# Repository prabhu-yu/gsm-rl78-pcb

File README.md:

# GSM-RL78-PCB

- Designed using KiCAD PCB Design SW.
- GSM modem Interface to RL78 uC using AT-MODEM commands over UART. Using this, we can build 2G/3G/4G wireless automation device. 
    - For example: to switch a remote high power motors, to monitor status using SMS/phone call. 
- The embedded C code to issue GSM AT Commands is available in another repo in my same gitHub account.

I plan to write a better documentation on my personal site:  
[https://prabhu-yu.github.io/](https://prabhu-yu.github.io/)

-
Thank You.  
Prabhu. Ullagaddi.

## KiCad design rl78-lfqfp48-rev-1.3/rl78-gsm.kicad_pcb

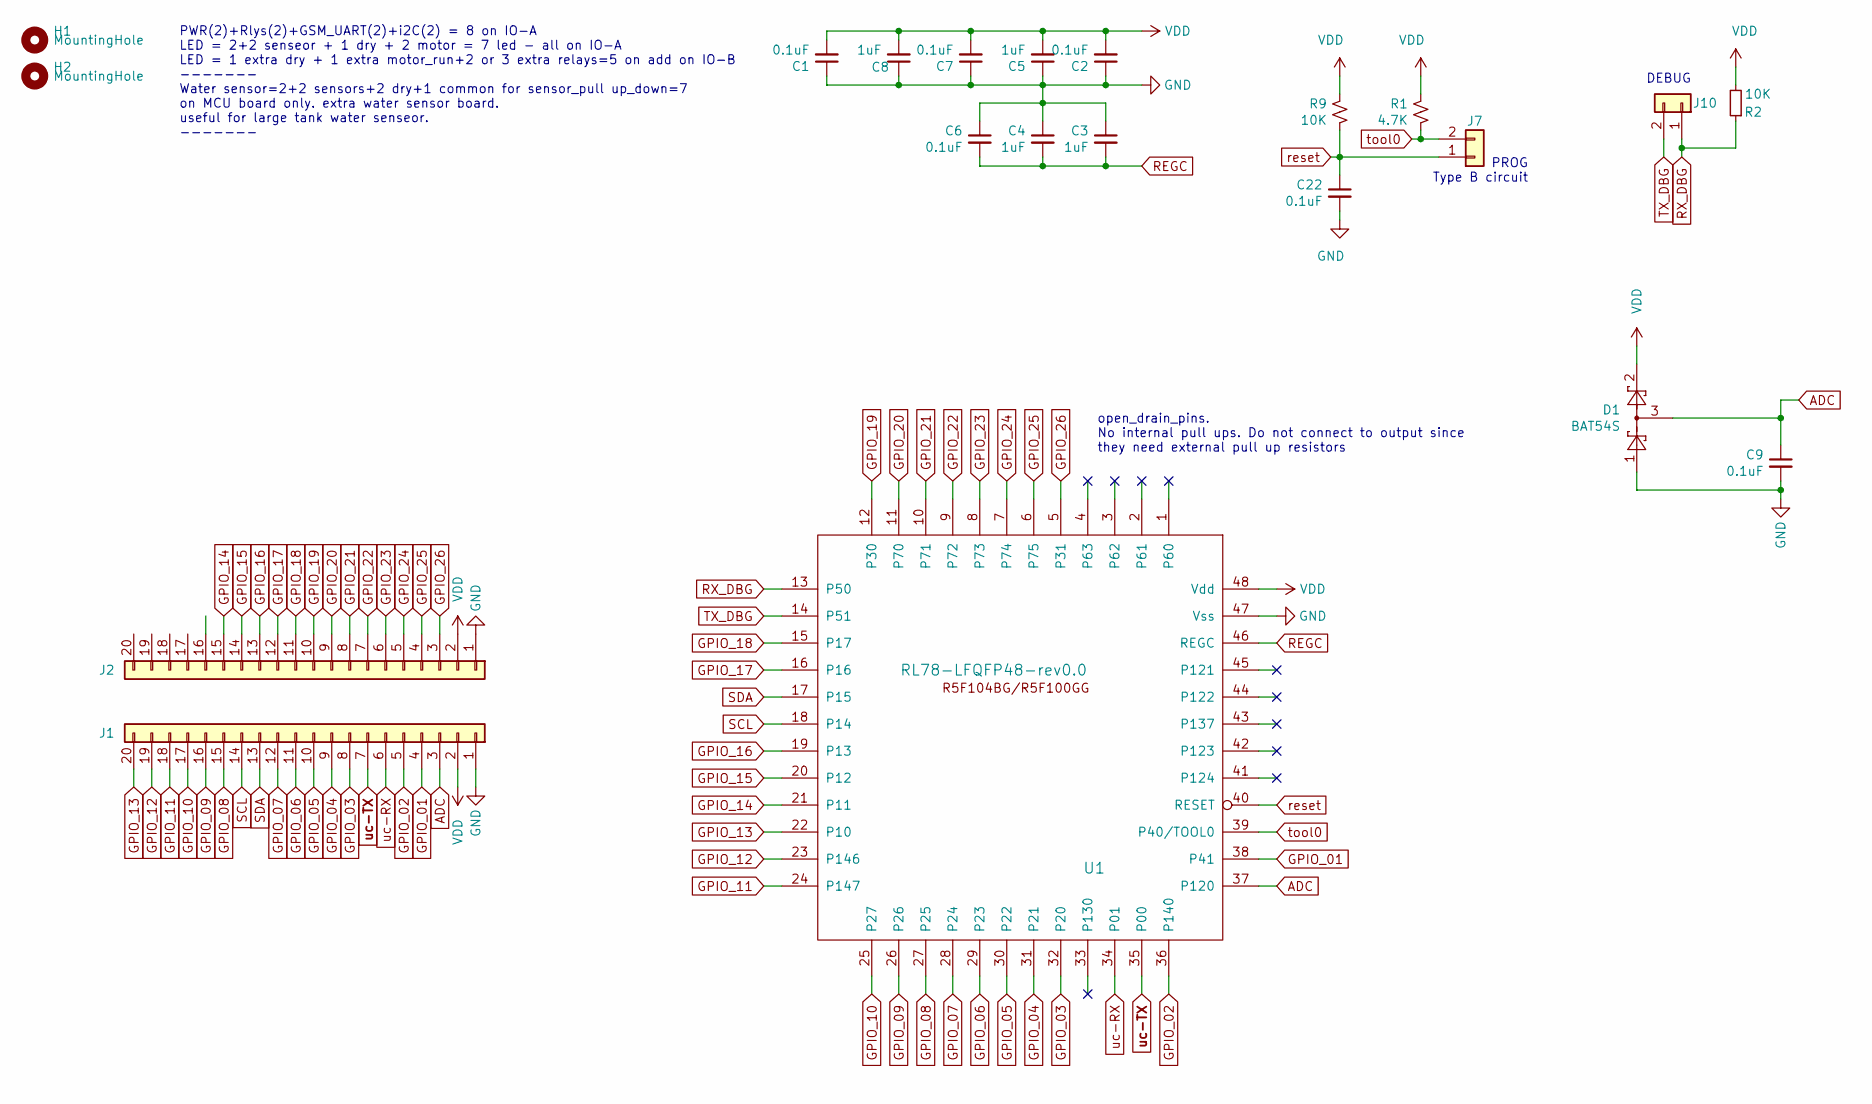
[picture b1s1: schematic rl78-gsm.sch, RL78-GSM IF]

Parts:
C1, C2, C6, C7, C9, C22: 0.1uF; C_1206_3216Metric_Pad1.33x1.80mm_HandSolder
C3, C4, C5, C8: 1uF; C_1206_3216Metric_Pad1.33x1.80mm_HandSolder
D1: BAT54S; SOT-23
H1, H2: MountingHole; MountingHole_4mm
J1, J2: Conn_01x20; PinHeader_1x20_P2.54mm_Vertical
J7, J10: Conn_01x02; PinHeader_1x02_P2.54mm_Vertical
R1: 4.7K; R_1206_3216Metric_Pad1.30x1.75mm_HandSolder
R2, R9: 10K; R_1206_3216Metric_Pad1.30x1.75mm_HandSolder
U1: RL78-LFQFP48-rev0.0; LQFP-48_7x7mm_P0.5mm

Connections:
ADC: C9.1, D1.3, J1.3, U1.37 (P120)
GND: C1.1, C2.1, C3.1, C4.1, C5.1, C6.1, C7.1, C8.1, C9.2, C22.2, D1.1, J1.1, J2.1, U1.47 (Vss)
GPIO_01: J1.4, U1.38 (P41)
GPIO_02: J1.5, U1.36 (P140)
GPIO_03: J1.8, U1.32 (P20)
GPIO_04: J1.9, U1.31 (P21)
GPIO_05: J1.10, U1.30 (P22)
GPIO_06: J1.11, U1.29 (P23)
GPIO_07: J1.12, U1.28 (P24)
GPIO_08: J1.15, U1.27 (P25)
GPIO_09: J1.16, U1.26
GPIO_10: J1.17, U1.25 (P27)
GPIO_11: J1.18, U1.24 (P147)
GPIO_12: J1.19, U1.23 (P146)
GPIO_13: J1.20, U1.22 (P10)
GPIO_14: J2.15, U1.21 (P11)
GPIO_15: J2.14, U1.20 (P12)
GPIO_16: J2.13, U1.19 (P13)
GPIO_17: J2.12, U1.16
GPIO_18: J2.11, U1.15 (P17)
GPIO_19: J2.10, U1.12 (P30)
GPIO_20: J2.9, U1.11 (P70)
GPIO_21: J2.8, U1.10 (P71)
GPIO_22: J2.7, U1.9 (P72)
GPIO_23: J2.6, U1.8 (P73)
GPIO_24: J2.5, U1.7 (P74)
GPIO_25: J2.4, U1.6 (P75)
GPIO_26: J2.3, U1.5 (P31)
REGC: C3.2, C4.2, C6.2, U1.46 (REGC)
RX_DBG: J10.1, R2.1, U1.13 (P50)
SCL: J1.14, U1.18 (P14)
SDA: J1.13, U1.17 (P15)
TX_DBG: J10.2, U1.14 (P51)
VDD: C1.2, C2.2, C5.2, C7.2, C8.2, D1.2, J1.2, J2.2, R1.2, R2.2, R9.2, U1.48 (Vdd)
reset: C22.1, J7.1, R9.1, U1.40 (RESET)
tool0: J7.2, R1.1, U1.39 (P40/TOOL0)
uc-RX: J1.6, U1.34 (P01)
uc-TX: J1.7, U1.35 (P00)

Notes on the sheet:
PWR(2)+Rlys(2)+GSM_UART(2)+i2C(2) = 8 on IO-A LED = 2+2 senseor + 1 dry + 2 motor = 7 led - all on IO-A LED = 1 extra dry + 1 extra motor_run+2 or 3 extra relays=5 on add on IO-B ------- Water sensor=2+2 sensors+2 dry+1 common for sensor_pull up_down=7 on MCU board only. extra water sensor board. u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
DEBUG
open_drain_pins. No internal pull ups. Do not connect to output since they need external pull up resistors
PROG Type B circuit

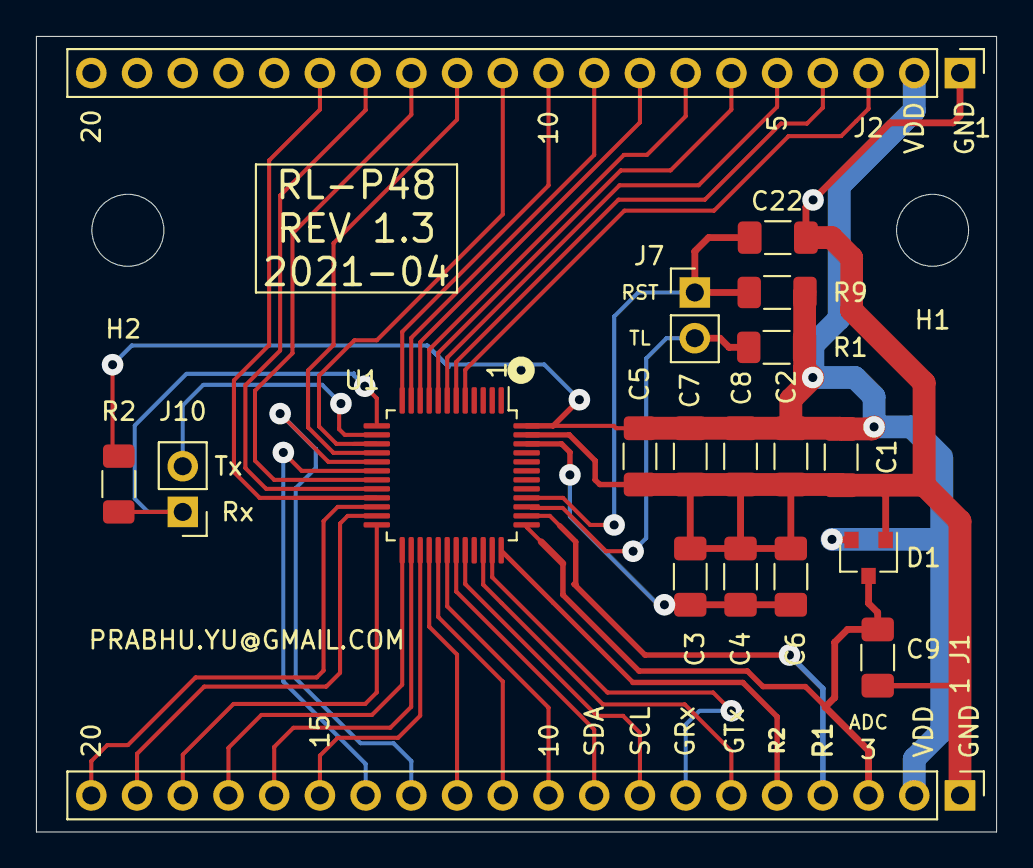
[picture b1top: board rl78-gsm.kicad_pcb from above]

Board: 2 copper layers, 53.3 x 44.2 mm, 21 parts (0 on the bottom side), 38 nets.

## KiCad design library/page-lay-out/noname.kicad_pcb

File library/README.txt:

kicad-library-master is downloaded from
https://github.com/automote/kicad-library

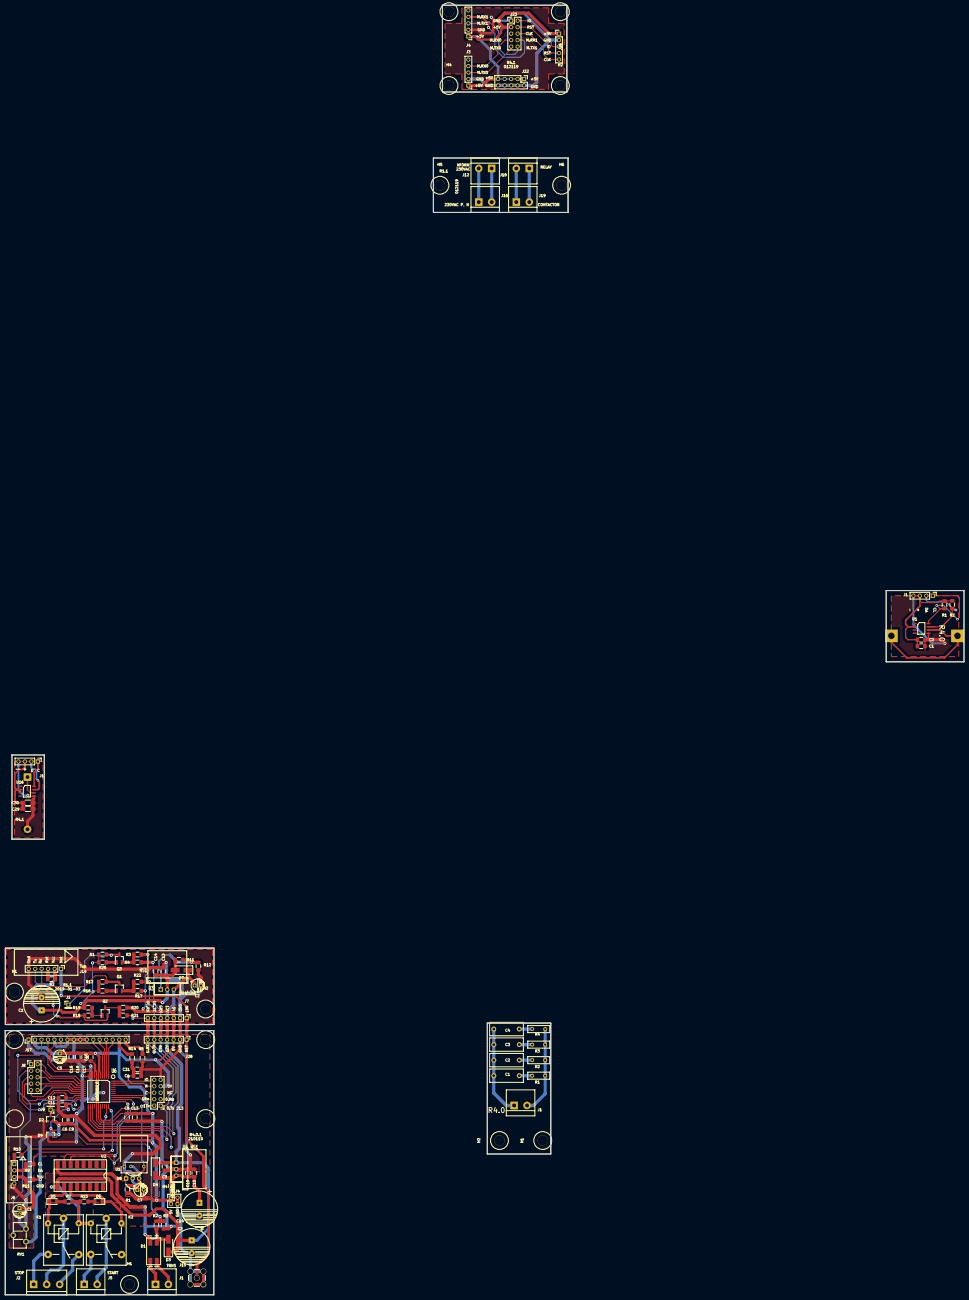
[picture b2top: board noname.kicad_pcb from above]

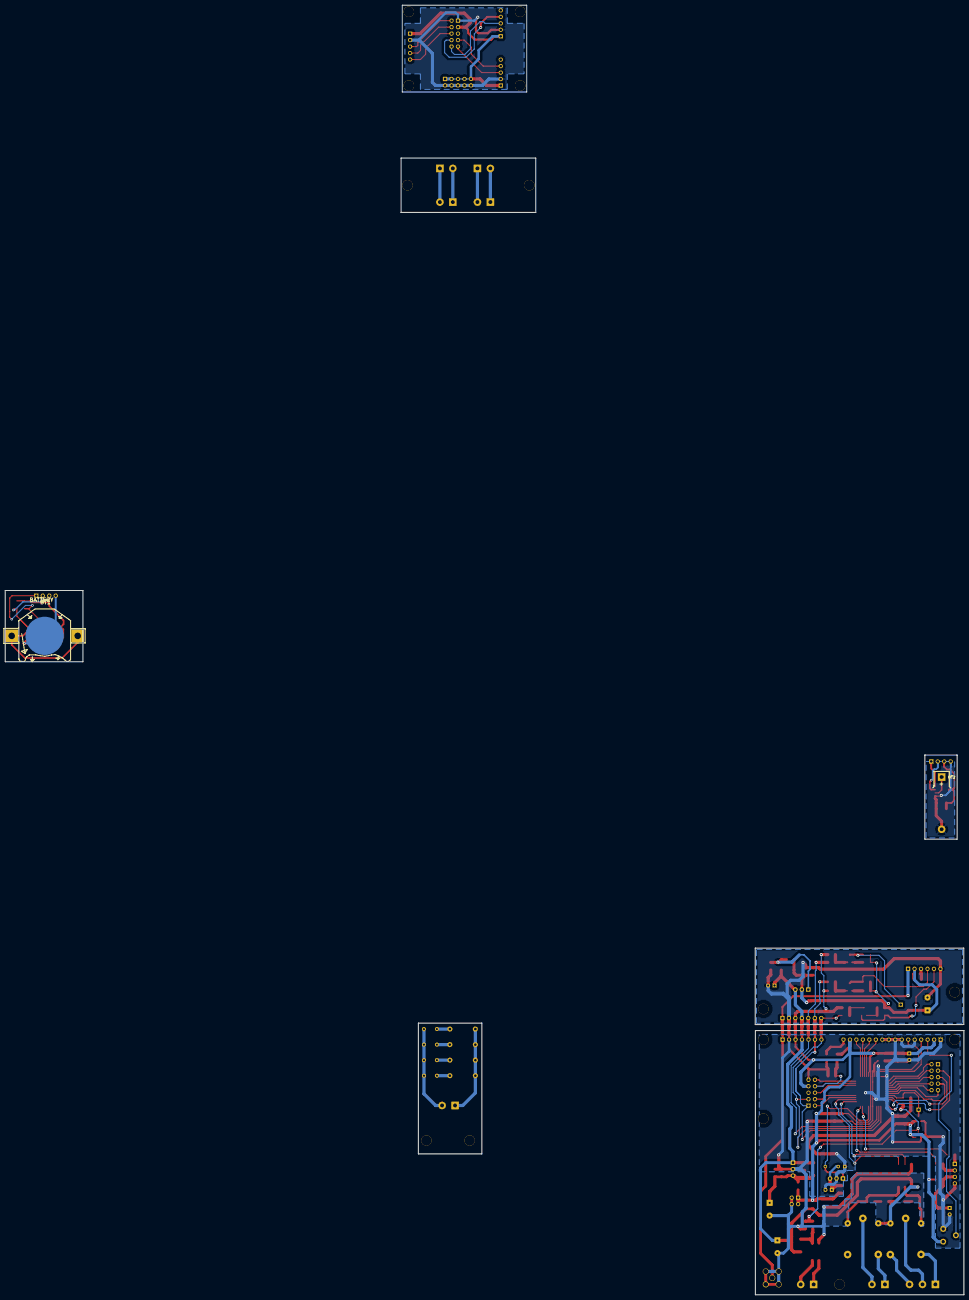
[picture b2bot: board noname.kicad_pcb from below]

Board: 2 copper layers, 376.0 x 505.8 mm, 127 parts (2 on the bottom side), 96 nets.

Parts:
BT1: BATTERY; BC-2001
BT2: BATTERY; Keystone_103_1x20mm-CoinCell-prabhu
C1: 6.8uF+; CP_Radial_D5.0mm_P2.50mm
C1#2: 1000uF/25V; CP_Radial_D14.0mm_P5.00mm
C1#3: C29; C_1206_3216Metric_Pad1.42x1.75mm_HandSolder
C1#4, C2#4, C3#2, C4#2: 0.01uF/X2/Y2; C_Rect_L13.0mm_W5.0mm_P10.00mm_FKS3_FKP3_MKS4
C2: 1000uF/50V; CP_Radial_D14.0mm_P5.00mm
C2#2: 10-100uF/50V; CP_Radial_D5.0mm_P2.50mm
C2#3: C30; C_1206_3216Metric_Pad1.42x1.75mm_HandSolder
C3: 0.1uF; R_1206_3216Metric_Pad1.42x1.75mm_HandSolder
C4, C8, C10, C14#2, C16, C18: 0.1uF; C_1206_3216Metric_Pad1.42x1.75mm_HandSolder
C5: 100uF; CP_Radial_D5.0mm_P2.50mm
C6, C9, C13, C13#2, C15, C17, C19, C31: 1uF; C_1206_3216Metric_Pad1.42x1.75mm_HandSolder
C7: 4.7uF/10V; CP_Radial_D5.0mm_P2.50mm
C11, C12: 0.01uF/ADC; C_1206_3216Metric_Pad1.42x1.75mm_HandSolder
C14: 1000uF/10V; CP_Radial_D14.0mm_P5.00mm
C29: 1uF; R_1206_HandSoldering
C30: 0.1uF; R_1206_HandSoldering
D1: D_Bridge_+-AA; MBXS
D2, D9: BAT54S; SOT-23
D3, D4: M7; D_SMA_Handsoldering
D5, D6: LED_Small; LED_1206_3216Metric_Pad1.42x1.75mm_HandSolder
D7: D; D_SMA_Handsoldering
D8: RPM7140; Vishay_MOLD-3Pin
H1, H1#2, H1#3, H1#4, H2, H2#2, H2#3, H3, H4, H5, H6: MountingHole; MountingHole_4.1x7.1mm
HS1, HS1#2: Heatsink; TO220_VERT-heatSink-Only
J1, J5, J12, J16, J18, J19: Screw_Terminal_1x02; bornier2
J1#2, J9: Conn_01x01; PinHeader_1x01_P2.54mm_Vertical
J1#3: Conn_01x04; Pin_Header_Straight_1x04_Pitch2.54mm
J1#4: Conn_01x04; PinHeader_1x04_P2.54mm_Vertical
J1#5: Screw_Terminal_01x02; bornier2
J2: Screw_Terminal_01x03; bornier3
J3, J4#2, J26: Conn_01x05; PinHeader_1x05_P2.54mm_Vertical
J4: Conn_02x02_Odd_Even; PinHeader_2x02_P2.54mm_Vertical
J6: Conn_01x04; RTC-BERG-V2
J7, J28: Conn_01x07; PinHeader_1x07_P2.54mm_Vertical
J8, J13, J22, J23: Conn_02x05_Odd_Even; PinHeader_2x05_P2.54mm_Vertical
J14: SIM800L-coro-board-v1; SIM800L-CoroBoard-Verticle
J15: Conn_Coaxial; SMA_THT_Jack_Straight
J17: LCD_2X16; LCD-v3
K1, K2: HRS4; Relay_SPDT_SANYOU_SRD_Series_Form_C
Q1, Q2, Q3: BC817; SOT-23_Handsoldering
R1: 60R-100R; R_1206_3216Metric_Pad1.42x1.75mm_HandSolder
R1#2, R26: 4K7-DNP; R_1206_3216Metric_Pad1.42x1.75mm_HandSolder
R1#3, R2#2, R2#3, R18: 47K; R_1206_3216Metric_Pad1.42x1.75mm_HandSolder
R1#4, R2#4, R3#3, R4#3: 100R; R_Box_L8.4mm_W2.5mm_P5.08mm
R2, R4: 1K2; R_1206_3216Metric_Pad1.42x1.75mm_HandSolder
R3: 150R; R_1206_3216Metric_Pad1.42x1.75mm_HandSolder
R3#2: 47K-DNP; R_1206_3216Metric_Pad1.42x1.75mm_HandSolder
R4#2, R20: 4.7K-DNP; R_1206_3216Metric_Pad1.42x1.75mm_HandSolder
R5: 1K+; R_1206_3216Metric_Pad1.42x1.75mm_HandSolder
R7, R14, R15: 10K; R_1206_3216Metric_Pad1.42x1.75mm_HandSolder
R9, R10: 100R-150R; R_1206_3216Metric_Pad1.42x1.75mm_HandSolder
R11: 100R-330R; R_1206_3216Metric_Pad1.42x1.75mm_HandSolder
R11#2: 240R; R_1206_3216Metric_Pad1.42x1.75mm_HandSolder
R12: 560R; R_1206_3216Metric_Pad1.42x1.75mm_HandSolder
R13, R16: 4K7; R_1206_3216Metric_Pad1.42x1.75mm_HandSolder
R17: 47K/pullup?-DNP; R_1206_3216Metric_Pad1.42x1.75mm_HandSolder
R19: 4.7K; R_1206_3216Metric_Pad1.42x1.75mm_HandSolder
R21, R22: 1K; R_1206_3216Metric_Pad1.42x1.75mm_HandSolder
RV1: POT; Potentiometer_ACP_CA9-H5_Horizontal
U1: TSOP17xx; Vishay_CAST-3Pin-Horizontal-V1
U1#2: DS3231MZ-SO8N; SOIC-8_3.9x4.9mm_Pitch1.27mm
U2: ULN2003; DIP-16_W8.89mm_SMDSocket_LongPads
U3: LM317_3PinPackage; TO220_VERT-heat
U4: L7805; TO220_VERT-heat
U6: MKE0XZXXXVLD2_V3; TQFP44-prabhu
U16: DS3231MZ; SOIC-8_3.9x4.9mm_Pitch1.27mm

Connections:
12V_GSM: C2#2.1, D7.1, J7.4, U3.3
+5V: C5.1, C6.2, C8.2, C9.2, C13.2, C15.2, C16.2, C17.2, C18.2, D2.2, D9.2, J3.1, J4.1, J4.3, J4#2.1, J13.7, J17.2, J17.15, J22.1, J22.3, J22.5, J22.7, J22.9, J23.3, J26.1, J28.3, R1.1, R4.2, R11.1, R14.2, RV1.1, U6.5, U6.6, U6.28
+12V: C2.1, C3.1, D3.1, D4.1, J28.4, K1.5, K2.2, R7.2, R15.2, U2.9, U4.1
/5V_GSM: J7.3, R3#2.1, R17.1, R20.1
/DTR: J7.5, R4#2.1
/NET: J7.1, J14.1
/VBAT: BT1.1, U1#2.6
/uc.RX: J7.7, R21.2
/uc.TX: J7.6, R22.2
AC-1: D1.4, J1.2
AC-2: D1.3, J1.1
ADJ: R11#2.1, R12.2, U3.1
CLK: J13.6, U6.42
DBG-CLK: J23.6, J26.5
DBG-IO: J23.2, J26.3
DBG-RST: J23.4, J26.4
DBG-mcu-rx0: J3.4, J23.7
DBG-mcu-rx1: J4#2.4, J23.8
DBG-mcu-tx0: J3.3, J23.9
DBG-mcu-tx1: J4#2.3, J23.10
DIO: J13.10, U6.44
DS3231_GND: BT2.2, C29.1, C30.1, J1#3.4, U16.5
DS3231_SCL: J1#3.1, U16.8
DS3231_SDA: J1#3.2, U16.7
DS3231_VCC: C29.2, C30.2, J1#3.3, U16.2
GND: BT1.2, C1.2, C1#2.2, C1#3.2, C2.2, C2#2.2, C2#3.2, C3.2, C4.1, C5.2, C6.1, C7.2, C8.1, C9.1, C10.2, C11.2, C12.2, C13.1, C13#2.2, C14.2, C14#2.2, C15.1, C16.1, C17.1, C18.1, C19.2, C31.1, D1.2, D2.1, D8.2, D9.1, J1#4.4, J3.2, J4.2, J4.4, J4#2.2, J6.4, J7.2, J13.9, J14.6, J15.2, J17.1, J17.5, J17.7, J17.8, J17.9, J17.10, J22.2, J22.4, J22.6, J22.8, J22.10, J23.1, J26.2, J28.2, R3.1, R5.1, R12.1, RV1.3, U1.1, U1#2.5, U2.8, U4.2, U6.7, U6.8, U6.11, U6.27
GSM.4V2: C1#2.1, C13#2.1, C14#2.1, D7.2, J14.2, R1#2.1, R2#2.1, R11#2.2, R13.1, R16.1, R19.1, R26.1, U3.2
LCD1_RS: J17.4, U6.10
LCD2_EN: J17.6, U6.9
LCD3_DB4: J17.11, U6.4
LCD4_DB5: J17.12, U6.3
LCD5_DB6: J17.13, U6.2
LCD6_DB7: J17.14, U6.1
unnamed: BT2.1, U16.6
unnamed: C1.1, C1#4.1, C2#4.1, C3#2.1, C4#2.1, J1#5.1, J6.3, R11.2
unnamed: C1#4.2, R1#4.2
unnamed: C2#4.2, R2#4.2
unnamed: C3#2.2, R3#3.2
unnamed: C4#2.2, R4#3.2
unnamed: C7.1, D8.3, R1.2, U1.2
unnamed: C10.1, C14.1, C19.1, D4.2, R4.1, U4.3
unnamed: D1.1, D3.2, R2.2
unnamed: D5.1, K1.2, U2.10
unnamed: D5.2, R7.1
unnamed: D6.1, K2.5, U2.11
unnamed: D6.2, R15.1
unnamed: D8.1, U1.3, U6.29
unnamed: J1#2.1, Q3.3, R1#2.2
unnamed: J1#5.2, R1#4.1, R2#4.1, R3#3.1, R4#3.1
unnamed: J6.1, R10.2
unnamed: J6.2, R9.2
unnamed: J8.2, U6.12
unnamed: J8.3, U6.22
unnamed: J8.4, U6.13
unnamed: J8.5, U6.21
unnamed: J8.6, U6.14
unnamed: J8.7, U6.18
unnamed: J8.8, U6.15
unnamed: J8.9, U6.17
unnamed: J8.10, U6.16
unnamed: J12.1, J16.2
unnamed: J12.2, J16.1
unnamed: J14.3, R2#2.2
unnamed: J14.4, Q1.3, R13.2
unnamed: J14.5, Q2.2, R18.2
unnamed: J15.1, J28.1
unnamed: J17.3, RV1.2
unnamed: J17.16, R5.2
unnamed: J18.1, J19.2
unnamed: J18.2, J19.1
unnamed: Q1.1, R16.2
unnamed: Q1.2, R17.2, R22.1
unnamed: Q2.1, R18.1, R19.2
unnamed: Q2.3, R20.2, R21.1
unnamed: Q3.1, R26.2
unnamed: Q3.2, R3#2.2, R4#2.2
PTA2_I2C0_SDA: R9.1, U6.33
PTA3_I2C0_SCL: R10.1, U6.32
RST: C4.2, C31.2, J13.8, R14.1, U6.43
SCL: J1#4.1, R1#3.2, U1#2.8
SDA: J1#4.2, R2#3.2, U1#2.7
SIM-DTR: J28.5, U6.25
THICK1: J5.2, K2.1
THICK2: J5.1, K2.3
THICK3: J2.1, K1.3
THICK4: J2.2, K1.1
THICK5: J2.3, K1.4
VCC: C1#3.1, C2#3.1, J1#4.3, R1#3.1, R2#3.1, U1#2.2
i-MON: C12.1, D2.3, J9.1, U6.19
in-1: U2.7, U6.34
in-2: U2.6, U6.35
uc.0.Rx: J13.3, J28.7, U6.24
uc.0.Tx: J13.1, J28.6, U6.23
uc.uart1.Rx: J13.4, U6.37
uc.uart1.Tx: J13.2, U6.36
v-MON: C11.1, D9.3, R2.1, R3.2, U6.20

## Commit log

2021-11-08 init
2021-11-08 reset
